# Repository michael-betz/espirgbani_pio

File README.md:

# The ESP32 Pinball RGB Animation clock

Display the time and animations on HUB75 LED panels.

  * Anti aliased fonts
  * Full unicode support (emojis!)
  * Python .ttf font converter tool
  * Alpha blending
  * Background shaders
  * USB-PD powered. Can drive the two 64 x 32 panels at full brightness. The LED turns on if PD negotiation succeeded. Otherwise the clock will run in low-power mode
  * Ambient light sensor

[Video of how it looks like](https://www.youtube.com/watch?v=0dwTC5q5t4M)

[Older writeup](http://yetifrisstlama.blogspot.com/2018/02/the-esp32-pinball-rgb-matrix-animation.html)

# Building
Needs [platform.io](https://platformio.org/) installed.

To install the toolchain and build the project:

```bash
$ pio run
```

Connect USB cable and upload the SPIFFS file system:

```bash
$ pio run -t uploadfs
```

Upload the firmware and show the serial console:

```bash
$ pio run -t upload -t monitor
```

# SD card instructions
Format as FAT32, then copy the following files:
  * `./settings.json`
  * `./animations.img`
  * `./fnt/{d}.fnt`

The .fnt files can be generated from .ttf files with `dev/font_converter.py`.

## `settings.json`
If this file does not exist or cannot be parsed, a new file with default settings will be created.

Once the clock is connected to the network, `settings.json` can be edited in the web-interface at `http://espirgbani.local/`.

```json
{
    "panel_io": {
        "CLK": 13,
        "R1": 22,
        "G1": 23,
        "B1": 21,
        "R2": 18,
        "G2": 19,
        "B2": 5,
        "A": 16,
        "B": 17,
        "C": 2,
        "D": 4,
        "E": 32,
        "LAT": 15,
        "OE_N": 33
    },
    "panel": {
        "test_pattern": true,
        "tp_brightness": 10,
        "low_power_brightness": 20,
        "is_clk_inverted": true,
        "clkm_div_num": 4,
        "max_frame_rate": 30,
        "is_gamma": false,
        "is_locked": true
    },
    "delays": {
        "font": 3600,
        "color": 600,
        "ani": 30,
        "shader": 400
    },
    "power": {
        "mode": 1,
        "offset": 0,
        "divider": 400,
        "max_limit": 100,
        "min_limit": 2,
        "day": {
            "h": 9,
            "m": 0,
            "p": 20
        },
        "night": {
            "h": 22,
            "m": 45,
            "p": 2
        }
    },
    "wifis": {
        "INSERT_SSID": "INSERT_PASSWORD"
    },
    "hostname": "espirgbani",
    "log_level":    {
        "*":    3,
        "httpd_sess":   2,
        "httpd_txrx":   2,
        "httpd_ws": 2,
        "httpd_server": 2,
        "httpd_parse":  2,
        "httpd":    2,
        "spi_master":   2,
        "vfs_fat":  2,
        "wifi": 2
    },
    "timezone": "CET-1CEST,M3.5.0,M10.5.0/3",
    "ntp_host": "pool.ntp.org"
}
```

### `panel_io` section
This section allows you to customize which pins are used on the ESP32 to connect to the panel pins.
The numbers are ESP32 GPIO numbers.

For example, if you run the test-pattern and notice that the red and green colors are swapped,
you can swap their pins on the ESP32 like so:

```json
    "panel_io": {
        "R1": 23,
        "G1": 22,
        "R2": 19,
        "G2": 18
    }
```

### `panel` section
Not all LED panels are the same. Here the timing parameters of the I2S panel driver can be configured.

  * `test_pattern`: if `true`, enters a LED panel test mode instead of normal operation
  * `tp_brightness`: brightness of the test pattern, from 1 to 127. Current draw gets ridiculous for the higher values
  * `low_power_brightness`: maximum brightness if USB-PD negotiation fails (if running from 5 V)
  * `is_clk_inverted`: if `false`, data changes on the rising clock edge. If `true`, data is stable on the rising clock edge (most panels need `true`)
  * `clkm_div_num`: sets the I2S clock divider from 2 to 128. Set it too high and get flicker, too low get ghost pixels. Flicker can be improved at the cost of color depth by reducing `BITPLANE_CNT` in `rgb_led_panel.h`.
  `"clkm_div_num": 4` corresponds to a 10 MHz pixel clock
  * `max_frame_rate`: the global maximum frame-rate limit in [Hz]. The background shader is updated at this rate. If the value is too large, freertos will become unresponsive
  * `is_gamma`: apply gamma correction to LED brightness
  * `is_locked`: stop screen updates while the clock numerals are written. Prevents tearing artifacts at the cost of a short freeze of the background shader

### `delays` section
controls delays between random animations, color and font changes.
They are all specified in [seconds]. The defaults are:

  * Randomize clock font every 3600 s (60 min)
  * Randomize outline color every 600 s (10 min)
  * Play a new pinball animation every 15 s
  * Randomize the background shader every 300 s (5 min). Set `shader` to <= 0 to always have a black background

### `power` section
controls the display brightness. Set the `mode` parameter to 0, 1 or 2 to select the control mode.

__mode 0: constant brightness__

Brightness is always the same and specified in `day.p` as a number from 0 to 127.

__mode 1: use ambient light sensor__

Brightness is set according to the measured ambient light. The sensor returns a number `x` from 0 - 4095 for a measured light level of roughly 10 - 1000 lux.

A linear equation is used to calculate the brightness: `p = (x - offset) / divider`.

The calculated value is limited to the range of `min_limit` to `max_limit` and applied as the panel brightness.

__mode 2: time based switching__

Brightness is set according to the current time. There is a `day` and `night` value, specified in `p` as a number from 0 to 127.

  * In the example, day-mode starts at `9:00` with brightness `20`
  * night-mode starts at `22:45` with brightness `2`

### `wifis` section
Add one or more wifi credentials. The key should be set to the SSID, the value to the wifi password.
If disconnected, the ESP will try to connect to the known wifi with the strongest signal every minute.

If the wifis section is empty or does not exist, the ESP will not try to connect to any wifis.

In any case, push the button on the PCB for > 1 s to toggle between Access Point and station mode.

### `hostname`
The hostname, which is the address where the ESP is reachable from the browser, can be customized here.

### `log_level`
Configure the esp-idf logging library. The key is the logging tag or `*` for everything.

The value the logging level

  * 0 = no logging
  * 1 = errors
  * 2 = warning
  * 3 = info
  * 4 = debug

See https://docs.espressif.com/projects/esp-idf/en/stable/esp32/api-reference/system/log.html

### `timezone`
is the local timezone in [TZ format](https://www.gnu.org/software/libc/manual/html_node/TZ-Variable.html). Look it up [here](https://github.com/nayarsystems/posix_tz_db/blob/master/zones.csv).

### `ntp_host`
The server used for time synchronization.

# TODO
  * fix hardware errors (4 botch wires), use MMC pins for SD card
  * http API support (easy use from curl)
  * wifi button support (access point on button press)
  * mqtt support?
  * update image from serial terminal

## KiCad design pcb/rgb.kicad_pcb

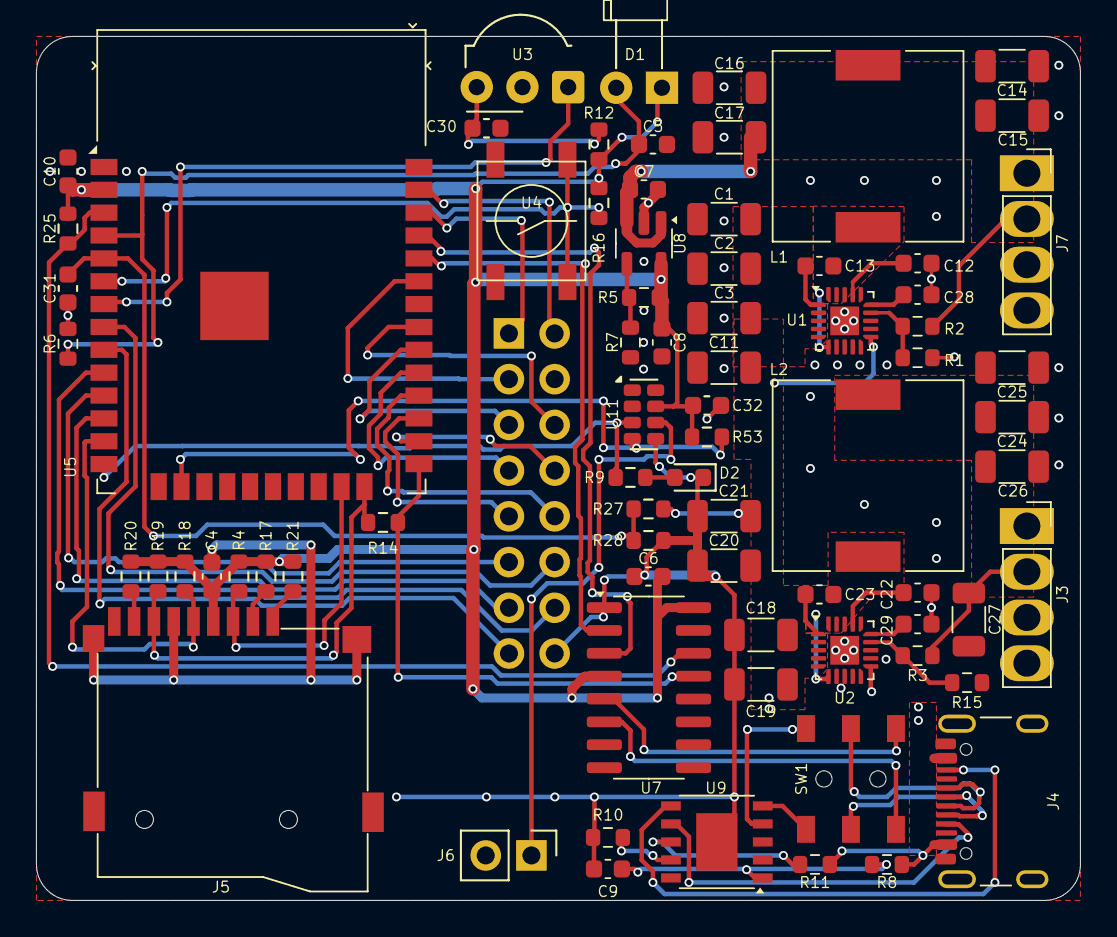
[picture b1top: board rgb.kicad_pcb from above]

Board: 2 copper layers, 58.0 x 48.0 mm, 76 parts (1 on the bottom side), 60 nets.

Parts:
C1, C2, C3, C11, C14, C15, C16, C17, C18, C19, C20, C21, C24, C25, C26, C27: 10u; C_1206_3216Metric
C4, C5, C6, C7, C8, C9, C10, C12, C13, C22, C23, C28, C29, C30, C31, C32: 2u2; C_0603_1608Metric
D1: ALS-PDIC144-6C/L378; LED_D3.0mm_Horizontal_O3.81mm_Z6.0mm
D2: GRN; LED_0603_1608Metric
J1: 2.54-2*8P; PinSocket_2x08_P2.54mm_Vertical
J3, J7: B4PS-VH; PinSocket_1x04_P2.54mm_Vertical
J4: TYPE-C-31-M-12; USB_C_Receptacle_GCT_USB4105-xx-A_16P_TopMnt_Horizontal
J5: TF-01A
J6: V_BATT; PinHeader_1x02_P2.54mm_Vertical
L1, L2: SMDRH104R-4R7NT
R1, R3, R4, R11, R16, R17, R18, R19, R20, R21, R25, R53: 10k; R_0603_1608Metric
R2, R15: 1k37; R_0603_1608Metric
R5: 37k4; R_0603_1608Metric
R6, R27: 47k; R_0603_1608Metric
R7: 19k8; R_0603_1608Metric
R8, R9, R14: 1k; R_0603_1608Metric
R10: 24k; R_0603_1608Metric
R12: 100R; R_0603_1608Metric
R28: 220k; R_0603_1608Metric
SW1: MS-22C01-G010; MS-22C01
U1, U2: SY8286ARAC; QFN-20-1EP_3x3mm_P0.45mm_EP1.6x1.6mm
U3: IRM-56384; Vishay_MOLD-3Pin
U4: EVQQ2
U5: ESP32-WROOM-32E; ESP32-WROOM-32D
U7: CH340C; SOIC-16_3.9x9.9mm_P1.27mm
U8: SPX3819M5-L; SOT-23-5
U9: CH224K; SSOP-10-1EP_3.9x4.9mm_P1.00mm
U11: RV-3028-C7; MicroCrystal_C7_SON-8_1.5x3.2mm_P0.9mm

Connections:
+3.3V: C4.1, C6.2, C8.1, C10.2, C32.1, D1.1 (K), J5.4 (VDD), R4.2, R5.2, R12.2, R16.2, R17.2, R18.2, R19.2, R20.2, R21.2, R25.2, R53.2, U5.2 (VDD), U7.4 (V3), U7.16 (VCC), U8.5 (OUT), U11.7 (VDD)
+5V: C7.2, C14.2 (K), C15.2 (K), C16.2 (K), C17.2 (K), J7.1, J7.2, L1.1, R1.1, U8.1 (IN), U8.3 (EN)
/A: J1.9, U5.27 (IO16)
/B: J1.10, U5.28 (IO17)
/B0: J1.3, U5.33 (IO21)
/B1: J1.7, U5.29 (IO5)
/C: J1.11, U5.11 (IO26)
/CC1: J4.A5 (CC1), U9.7 (CC1)
/CC2: J4.B5 (CC2), U9.6 (CC2)
/CLK: J1.13, U5.12 (IO27)
/D: J1.12, U5.8 (IO32)
/E: J1.8, U5.26 (IO4)
/G0: J1.2, U5.37 (IO23)
/G1: J1.6, U5.31 (IO19)
/OE: J1.15, U5.9 (IO33)
/R0: J1.1, U5.36 (IO22)
/R1: J1.5, U5.30 (IO18)
/RTC_SCL: R9.2, U5.14 (IO12), U11.3 (SCL)
/RTC_SDA: R53.1, U5.16 (IO13), U11.4 (SDA)
/SD_CLK: J5.5 (CLK), R18.1, U5.13 (IO14)
/SD_CMD: J5.3 (CMD), R4.1, U5.23 (IO15)
/SD_D0: J5.7 (DAT0), R14.2, R19.1, U5.24 (IO2)
/STB: J1.14, U5.10 (IO25)
/Stepdown_b/v_out: C24.2 (K), C25.2 (K), C26.2 (K), C27.2 (K), J3.1, J3.2, L2.1, R3.1
/USB_N: J4.A7 (D-), J4.B7 (D-), SW1.2 (B)
/USB_N_P: SW1.3 (C), U9.5 (DM)
/USB_N_S: SW1.1 (A), U7.6 (UD-)
/USB_P: J4.A6 (D+), J4.B6 (D+), SW1.5 (B)
/USB_P_P: SW1.4 (A), U9.4 (DP)
/USB_P_S: SW1.6 (C), U7.5 (UD+)
/esp_prog: R14.1, U5.25 (IO0), U7.13 (~DTR)
/esp_reset: R25.1, U5.3 (EN), U7.14 (~RTS)
/esp_rx: U5.34 (RXD0/IO3), U7.2 (TXD)
/esp_tx: U5.35 (TXD0/IO1), U7.3 (RXD)
GND: C1.1 (A), C2.1 (A), C3.1 (A), C4.2, C5.2, C6.1, C7.1, C8.2, C9.2, C10.1, C11.1 (A), C12.2 (K), C14.1 (A), C15.1 (A), C16.1 (A), C17.1 (A), C18.1 (A), C19.1 (A), C20.1 (A), C21.1 (A), C22.2 (K), C24.1 (A), C25.1 (A), C26.1 (A), C27.1 (A), C28.2 (K), C29.2 (K), C30.1, C31.2, C32.2, D2.1 (K), J1.4, J1.16, J3.3, J3.4, J4.A1 (GND), J4.A12 (GND), J4.B1 (GND), J4.B12 (GND), J4.S1 (SHIELD), J5.6 (VSS), J5.10 (SHIELD), J6.2, J7.3, J7.4, R2.2, R6.2, R7.1, R10.2, R15.2, R27.2, U1.7 (GND), U1.8 (GND), U1.12 (MODE), U1.18 (GND), U1.21 (GND), U2.7 (GND), U2.8 (GND), U2.12 (MODE), U2.18 (GND), U2.21 (GND), U3.2 (GND), U4.B, U4.B', U5.1 (GND), U5.15 (GND), U5.38 (GND), U5.39 (GND), U7.1 (GND), U8.2 (GND), U9.11 (GND), U11.5 (VSS)
unnamed: C12.1 (A), U1.17 (VCC)
unnamed: C13.1 (A), L1.2, U1.6 (LX), U1.19 (LX), U1.20 (LX)
unnamed: C13.2 (K), U1.1 (BS)
unnamed: C22.1 (A), U2.17 (VCC)
unnamed: C23.1 (A), L2.2, U2.6 (LX), U2.19 (LX), U2.20 (LX)
unnamed: C23.2 (K), U2.1 (BS)
unnamed: C28.1 (A), U1.15 (BYP)
unnamed: C29.1 (A), U2.15 (BYP)
unnamed: C5.1, D1.2 (A), R6.1, U5.4 (SENSOR_VP)
unnamed: D2.2 (A), R9.1
unnamed: J5.8 (DAT1), R20.1
unnamed: J5.1 (DAT2), R21.1
unnamed: J5.2 (DAT3/CD), R17.1
unnamed: J6.1, U11.6 (VBACKUP)
unnamed: R1.2, R2.1, U1.14 (FB)
unnamed: R3.2, R15.1, U2.14 (FB)
unnamed: U3.1 (OUT), U5.7 (IO35)
unnamed: C30.2, R12.1, U3.3 (Vs)
unnamed: R16.1, U4.A, U4.A', U5.6 (IO34)
unnamed: C31.1, R27.1, R28.2, U5.5 (SENSOR_VN)
unnamed: R5.1, R7.2, U8.4 (ADJ)
unnamed: R10.1, U9.9 (CFG1)
unnamed: R11.1, U9.8 (VBUS)
unnamed: C9.1, R8.1, U9.1 (VDD)
VBUS: C1.2 (K), C2.2 (K), C3.2 (K), C11.2 (K), C18.2 (K), C19.2 (K), C20.2 (K), C21.2 (K), J4.A4 (VBUS), J4.A9 (VBUS), J4.B4 (VBUS), J4.B9 (VBUS), R8.2, R11.2, R28.1, U1.2 (IN), U1.3 (IN), U1.4 (IN), U1.5 (IN), U1.11 (EN), U2.2 (IN), U2.3 (IN), U2.4 (IN), U2.5 (IN), U2.11 (EN)

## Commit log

2020-06-08 initial
2020-06-08 change debug level to 4
2020-06-08 Animations work (slightly choppy). Fonts not yet.
2020-06-09 background, clock and animations draw nicely
    * still need to look into the fast_seek patch again
    * brightness is not yet managed
2020-06-09 smooth animations, even without fast_seek
    * no more lost chars in web-console
    * replace 4 x spaces with tabs
2020-06-09 settings.json: rename tp_brightness to brightness
2020-06-09 measure uptime
2020-06-10 fix some naughty memory leaks
    also more NULL pointer checks, hopefully less reboots
2020-06-10 add esp-comms library from git
2020-06-10 readme
2020-06-10 add missing data/settings.htm
2020-06-10 fix settings prefix (b)
2020-06-11 add day/night mode
2020-06-11 re-shuffled tasks a bit
    ... to make better use of ram.
    There's still a race condition in the
    web-server code somewhere.
    Also, update time on full minutes.
2020-06-11 enable ota by default
2020-06-12 now based on ESPAsyncWebServer
2020-06-13 get rid of separate clock task
    * combined task for pinball animations and clock update
    * saves a lot of precious heap and stack
    * make max. frame-rate and layer sync. configurable
2020-06-13 better vertical alignment of font rendering
2020-06-14 font.cpp: do propper bounding box calculation
2020-06-14 font: use BB for centering, 2 digit filenames
2020-06-14 clean up logging a bit
2020-06-15 pin the 2 tasks to 2 cores
2020-06-15 i2s_parallel: disable double buffer, save 28k heap
2020-06-16 frame_buffer: pre-calculate 4 bit shades
2020-06-16 setFromFile(): flatten the for loop
2020-06-16 add radial laser shader
2020-06-16 fix bendy shader, add shader delay, color shades
2020-06-16 add missing ./data files for web-interface
2020-06-16 g_f_del: move declaration to rgb_led_panel.h
2020-06-16 add set_shade_h() for gamma corrected AA lines
2020-06-16 fix font pixels rolling around
2020-06-17 updateFrame(): performance enhancements
    * re-arrange the 3 loops to take getBlendedPixel() out of
    the innermost one
    * call getBlendendPixel() only once per pixel,
    not 7 times as before
    * remove remains of double buffer entirely
2020-06-17 fine tune laser shader
2020-06-18 fast_seek: override ff.c from library
    files are still original. Hack not yet applied.
2020-06-18 apply fast_seek hack: always enable it in ff.c
2020-06-18 organize fseek_hack in separate directory
2020-06-18 remove gamma correction
    it made things look much worse!
    Seems like rgb_led_panel.c is pretty true to colors already
2020-06-18 hard-code espressif32 platform version, update readme
2020-06-27 aaLine: mix colors
    removes artifacts when lines are drawn close together,
    like in the laser shader
2020-06-27 add float based AA line drawer
2020-11-05 fix time redraw lag (missing the seconds roll-over)
2023-11-02 common.h: set GPIO_SD_MISO to 12, compatible with REV1 PCB
    in the next revision of the PCB I would use GPIO35, but this
    doesn't exist yet (except for hacking REV1)
2024-10-19 add first try at rev 2 of the schematic
2024-10-19 pcb: exploration
2024-10-20 initial routing done
2024-10-22 turn esp by 90 deg
    rip-up, re-route
2024-10-22 optimize pinout
2024-10-23 finish routing
2024-10-23 solve DRC errors
2024-10-23 put a cool pattern on the bottom silk
2024-10-23 polish
2024-10-23 mostly ready for production. 18 $ / board in qty. 5
2024-10-23 add pattern to top silkscreen, order
2024-10-28 pcb: increase esp32 voltage slightly
2024-10-28 first step at getting rid of the arduino dependencies
2024-10-29 first steps towards rev2
2024-10-29 towards compilation
2024-10-29 this compiles
2024-10-29 add SD card init
2024-10-29 try to fix settings ,json on sd card
2024-11-02 jsonSettings: move back to Websocket based communication
2024-11-04 integrate settings.htm in index.htm, use websockets
2024-11-04 clean up index.htm a bit
2024-11-04 copy i2s settings from scope clock
    this should run at up to 40 MHz when cfg.clk_div = 2;
2024-11-04 run clang-format
2024-11-04 enable FAST_SEEK
2024-11-04 add ambient light sensor
2024-11-05 finish and document ambient light mode
    add custom partition layout
2024-11-05 fix a compiler warning
2024-11-05 implement low power mode
2024-11-05 add the power LED gpio
2024-11-05 led pins don't react yet
2024-11-06 fix i2s_parallel.c io_config function. clang-format align
2024-11-06 hardware bug, swap IO 12 and 33
2024-11-07 rework the websocket stuff
2024-11-12 update panel driver. doesn't work yet
2024-11-12 works but text draws slowly
2024-11-13 add log level and min. brightness to settings
    works but sth. is wrong with the SD card
2024-11-14 fix heap corruption in json_settings()
2024-11-15 tune ambient brightness and wifi auto connect
2024-11-15 remove the framebuffer lock. It did not have any advantage.
2024-11-16 make websocket logging work more robustly
    the browser now polls the log-buffer every second (query - response)
2024-11-16 dump complete log buffer on initial connection
2024-11-16 add optional gamma correction
2024-11-18 misc. bug fixes
    * run in TP mode without SD card
    * Use more accurate clock for RTC (80 MHz)
    * add single panel mode which centers the text on the
    first panel
2024-11-18 massive re-write of the whole font system. 10x faster now
    * get rid of bmfont dependency to generate font files
    * use similar font format as esp32_crt but serialized
    in a file on sd card
    * full unicode support (emojis, etc)
    * outline support
    * don't use .bmp file anymore (slow, inefficient)
2024-11-18 clean up font.c
    * set verbose logging
    * less global stuff in header file
2024-11-19 add font converter tool
2024-11-19 font converter is in good shape now
2024-11-19 test converting the first batch on fonts
    * fix bug in glyphToBuffer() when pixels get skipped
2024-11-20 work on outline
2024-11-21 add outline generation and preview
2024-11-21 less outline is more
2024-11-21 use fractional metrics for auto_tune_font_size()
    these metrics are not valid for the outline, but it
    doesn't matter because we calculate the font size from
    the non-outlined glyphs only.
2024-11-21 make outlint glyphs work
2024-11-21 add framebuffer lock to layer 2 again
2024-11-21 clang-format
2024-11-21 remove obsolete wifi build flags
2024-11-21 fix platform version
2024-11-22 add shader tester
2024-11-22 make SDL shader tester work
2024-11-23 improve the doom-flame shader
    * add wind-directions and flares
2024-11-24 comments to scaling function
2024-11-25 font format: support bitmap fonts and 1 bit bitmaps
2024-11-28 try emscripten compile
2025-01-09 schematic: one more item for the todo list
2025-01-15 first sketch of optimized pinout
    Support SD MMC mode x4
2025-01-15 finalize pinout
2025-01-15 messing, with the flame shader wind, not done yet
2025-01-23 add note about GPIO12 to schematic
2025-01-23 schematic: add a missing wire
2025-01-23 schematic: add jumper resistors to isolate SD card and panel pins
2025-01-23 sch: move comment
2025-02-09 do we have space fo the RTC?
2025-05-13 Add log-levels to settings.json, fix float overflow for lasers shader.
2025-05-13 switch espressif32 from 6.9 to 6.10, add HW_REV3
2025-05-13 add lemon.bdf as default font on spiffs
2025-05-14 add status messages on boot
2025-05-14 polished startup
2025-05-14 change color channel mapping for P4 panels
2025-05-19 update default settings
2025-09-07 sync up default_settings.json with the README.md
2025-09-08 animations.c: display the WIFI state decently on the panel
    * also make the push-button toggle between station and AP mode
2025-09-08 common.h: make GPIO_PD_BAD optional
    if not defined, the clock will never enter low-power mode
2025-09-08 pcb: add some items to the TODO list
    * detect 5 V operation with ADC
    * IR receiver
    * RTC chip
2025-09-12 settings.json: make the GPIO numbers of the panel customizable
2025-09-12 platformio.ini: upgrade to espressif@6.12
    * disable wifi when there are not entries in the settings.json
    * don't display the `WIFI: scanning ...` messages for the periodic
    reconnects
    * show local time in logs
2025-09-13 pcb: started to place components
    looks like the Rev: 3 PCB will be the same size as Rev: 2
2025-09-13 rev3 routing complete
2025-09-13 rev3 pcb: add IR receiver
2025-09-13 pcb: remove D1 data pin from SD card
    * 2 wire MMC mode does not exist. Can only use 1 wire anyway.
    * Use the freed up GPIO for address line E
2025-09-14 pcb: optimize GND plane
2025-10-04 improve error handling when readin animation file
    * change some animation and shader log statements to debug level
    * simplify shader selection logic. Any index < 4 means off
